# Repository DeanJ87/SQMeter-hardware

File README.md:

# SQMeter Hardware

Hardware source files for the [SQMeter](https://github.com/DeanJ87/SQMeter) open-source sky quality meter.

The main firmware, web UI, and documentation live in the **[SQMeter repo](https://github.com/DeanJ87/SQMeter)**. This repo is the canonical source of truth for the electronics design and manufacturing files.

---

## What's here

| Path | Contents |
|------|----------|
| `hardware/kicad/` | KiCad schematic and PCB source |
| `hardware/exports/` | Generated schematic SVG/PDF and PCB renders |
| `hardware/manufacturing/` | Gerbers, drill files, pick-and-place |
| `hardware/bom/` | Bill of materials (CSV and human-readable) |
| `hardware/ibom/` | InteractiveHtmlBom for assembly |
| `hardware/images/` | Board renders and preview images |
| `scripts/` | Export, BOM, iBOM, and release packaging scripts |

---

## Quick links

| | |
|--|--|
| Main docs site | <https://sqmeter.dev/> |
| Main repo | <https://github.com/DeanJ87/SQMeter> |
| Hardware releases | [Releases](../../releases) |
| Schematic PDF | TODO: link once first release is published |
| Schematic SVG | TODO: link once first release is published |
| BOM CSV | TODO: link once first release is published |
| InteractiveHtmlBom | TODO: link once first release is published |
| Gerbers ZIP | TODO: link once first release is published |

---

## Versioning

Hardware versions follow `vMAJOR.MINOR.PATCH` tied to physical board revisions.

- `v0.x.x` — prototype / bring-up
- `v1.0.0` — first stable public release

Hardware versions are independent of firmware versions. A firmware update does not require a new board revision.

---

## Generating exports locally

Requires KiCad 8 with `kicad-cli` on your PATH.

```bash
./scripts/export-kicad.sh      # schematic SVG/PDF + PCB renders + gerbers
./scripts/generate-bom.sh      # hardware/bom/bom.csv
./scripts/generate-ibom.sh     # hardware/ibom/ibom.html
./scripts/package-release.sh   # dist/SQMeter-Hardware-release.zip
```

---

## 3D printed enclosure

Enclosure files are hosted on Printables (TODO: add link when available). This repo focuses on PCB electronics and manufacturing assets. Mounting dimensions and interface notes may be added under `docs/assembly.md`.

---

## License

[MIT](LICENSE)

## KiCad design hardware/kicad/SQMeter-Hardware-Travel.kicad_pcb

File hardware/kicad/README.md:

# KiCad Project

KiCad 10 projects for the SQMeter boards. All are hardware revision A (`HW_REV` in
`../generator/design.py`), versioned separately from any firmware.

| Project | ESP32 | Power in | For |
|---------|-------|----------|-----|
| `SQMeter-Hardware-ETH.kicad_pro` | Waveshare ESP32-S3-ETH (+ PoE Module B) on 2x20 sockets | PoE or 12 V | Permanent home installs: wired Ethernet, one cable |
| `SQMeter-Hardware-Zero.kicad_pro` | Waveshare ESP32-S3-Zero-M on 2x9 sockets | 12 V | Cheap WiFi home board |
| `SQMeter-Hardware-DevKit.kicad_pro` | ESP32-S3-DevKitC-1-N16R8 on 2x22 sockets | 12 V | WiFi home board, 16 MB flash (always-on red LED) |
| `SQMeter-Hardware.kicad_pro` | ESP32-S3-WROOM-1-N16R8 soldered (JLC) | 12 V or USB-C | Fully assembled WiFi home board |
| `SQMeter-Hardware-Travel.kicad_pro` | Waveshare ESP32-S3-Zero-M on 2x9 sockets | USB-C + 1S Li-ion | Portable unit, 85 x 66 mm, no field wiring |

### GPIO maps

Module, DevKit, Zero and Travel share one map (limited by the Zero, whose 2.54 mm headers carry only
GPIO1-13). The ETH board's W5500 owns GPIO9-14, so it has its own:

| Function | Module / DevKit / Zero | Travel | ETH |
|---|---|---|---|
| RG-15 TX / RX (ESP side) | 1 / 2 | - | 15 / 16 |
| Wind vane (ADC1) / anemometer | 4 / 5 | - | 1 / 2 |
| I2C SDA / SCL (TSL2591 #1, MLX90614, BME280, spare/OLED) | 8 / 9 | 8 / 9 | 17 / 18 |
| I2C-2 SDA / SCL (TSL2591 #2) | 10 / 11 | 10 / 11 | 41 / 42 |
| GPS TX / RX (ESP side) | 12 / 13 | 12 / 13 | 47 / 48 |
| AUX | 6, 7 | 6, 7 | 39, 40 |
| Fuel gauge alert (MAX17048 ALRT, active low) | - | 1 | - |
| Charger STAT1 / STAT2 / PG (open drain, active low) | - | 2 / 4 / 5 | - |
| Status LED | 47 (module only) | Zero RGB 21 | ETH RGB 21 |

### Power

- **12 V boards:** P-FET reverse protection, polyfuse, TVS, AP6320x buck. Plug-in boards are fed 5 V
  through a Schottky and give 3V3 back for the sensors.
- **ETH:** PoE (or the ETH board's USB-C) gives 5 V on its VBUS pin; we feed its VSYS pin (after its own
  diode) from the 12 V buck, so the two never fight. On PoE the RG-15 gets 12.6 V from an MT3608 boost.
- **Travel:** sized for a 1S2P 18650 pack (~7 Ah). USB-C into an MCP73871 power-path charger in adapter
  mode (1.65 A input, backs off if the source sags below 4.55 V): runs the system while charging, 833 mA
  charge (~9 h from empty), safety timer off (it would expire before a 7 Ah pack is full), charges only
  between about 3 and 44 C (NTC on the board). DW01A + two AO3400A protect bare cells (over-charge,
  over-discharge, short). A MAX17048 fuel gauge on the main I2C bus (0x36) reports state of charge %, cell
  voltage and charge/discharge rate; the charger's STAT1/STAT2/PG pins give USB present / charging /
  charged / fault. The power switch cuts the system but not charging. The Zero's own USB-C stays inside for
  recovery flashing. Cells in parallel must be matched (same voltage) before connecting.

All five I2C ports share one JST-XH pinout: **1 GND, 2 3V3, 3 SDA, 4 SCL**. The TSL2591's address is fixed (0x29), so a second
one (SQM + SQM-L) goes on its own bus: the I2C-2 port.

## Files

Generated by `../generator/build.sh <module|devkit|zero>` (see its README); hand-tune in KiCad afterwards.
JLCPCB files (gerber zip, BOM, CPL) come from `../generator/export_jlc.sh <module|devkit|zero>` and land in
`../manufacturing/<project>-rev<X>/`.

Open the `.kicad_pro`, not the `.kicad_sch`/`.kicad_pcb` directly, so library associations resolve.

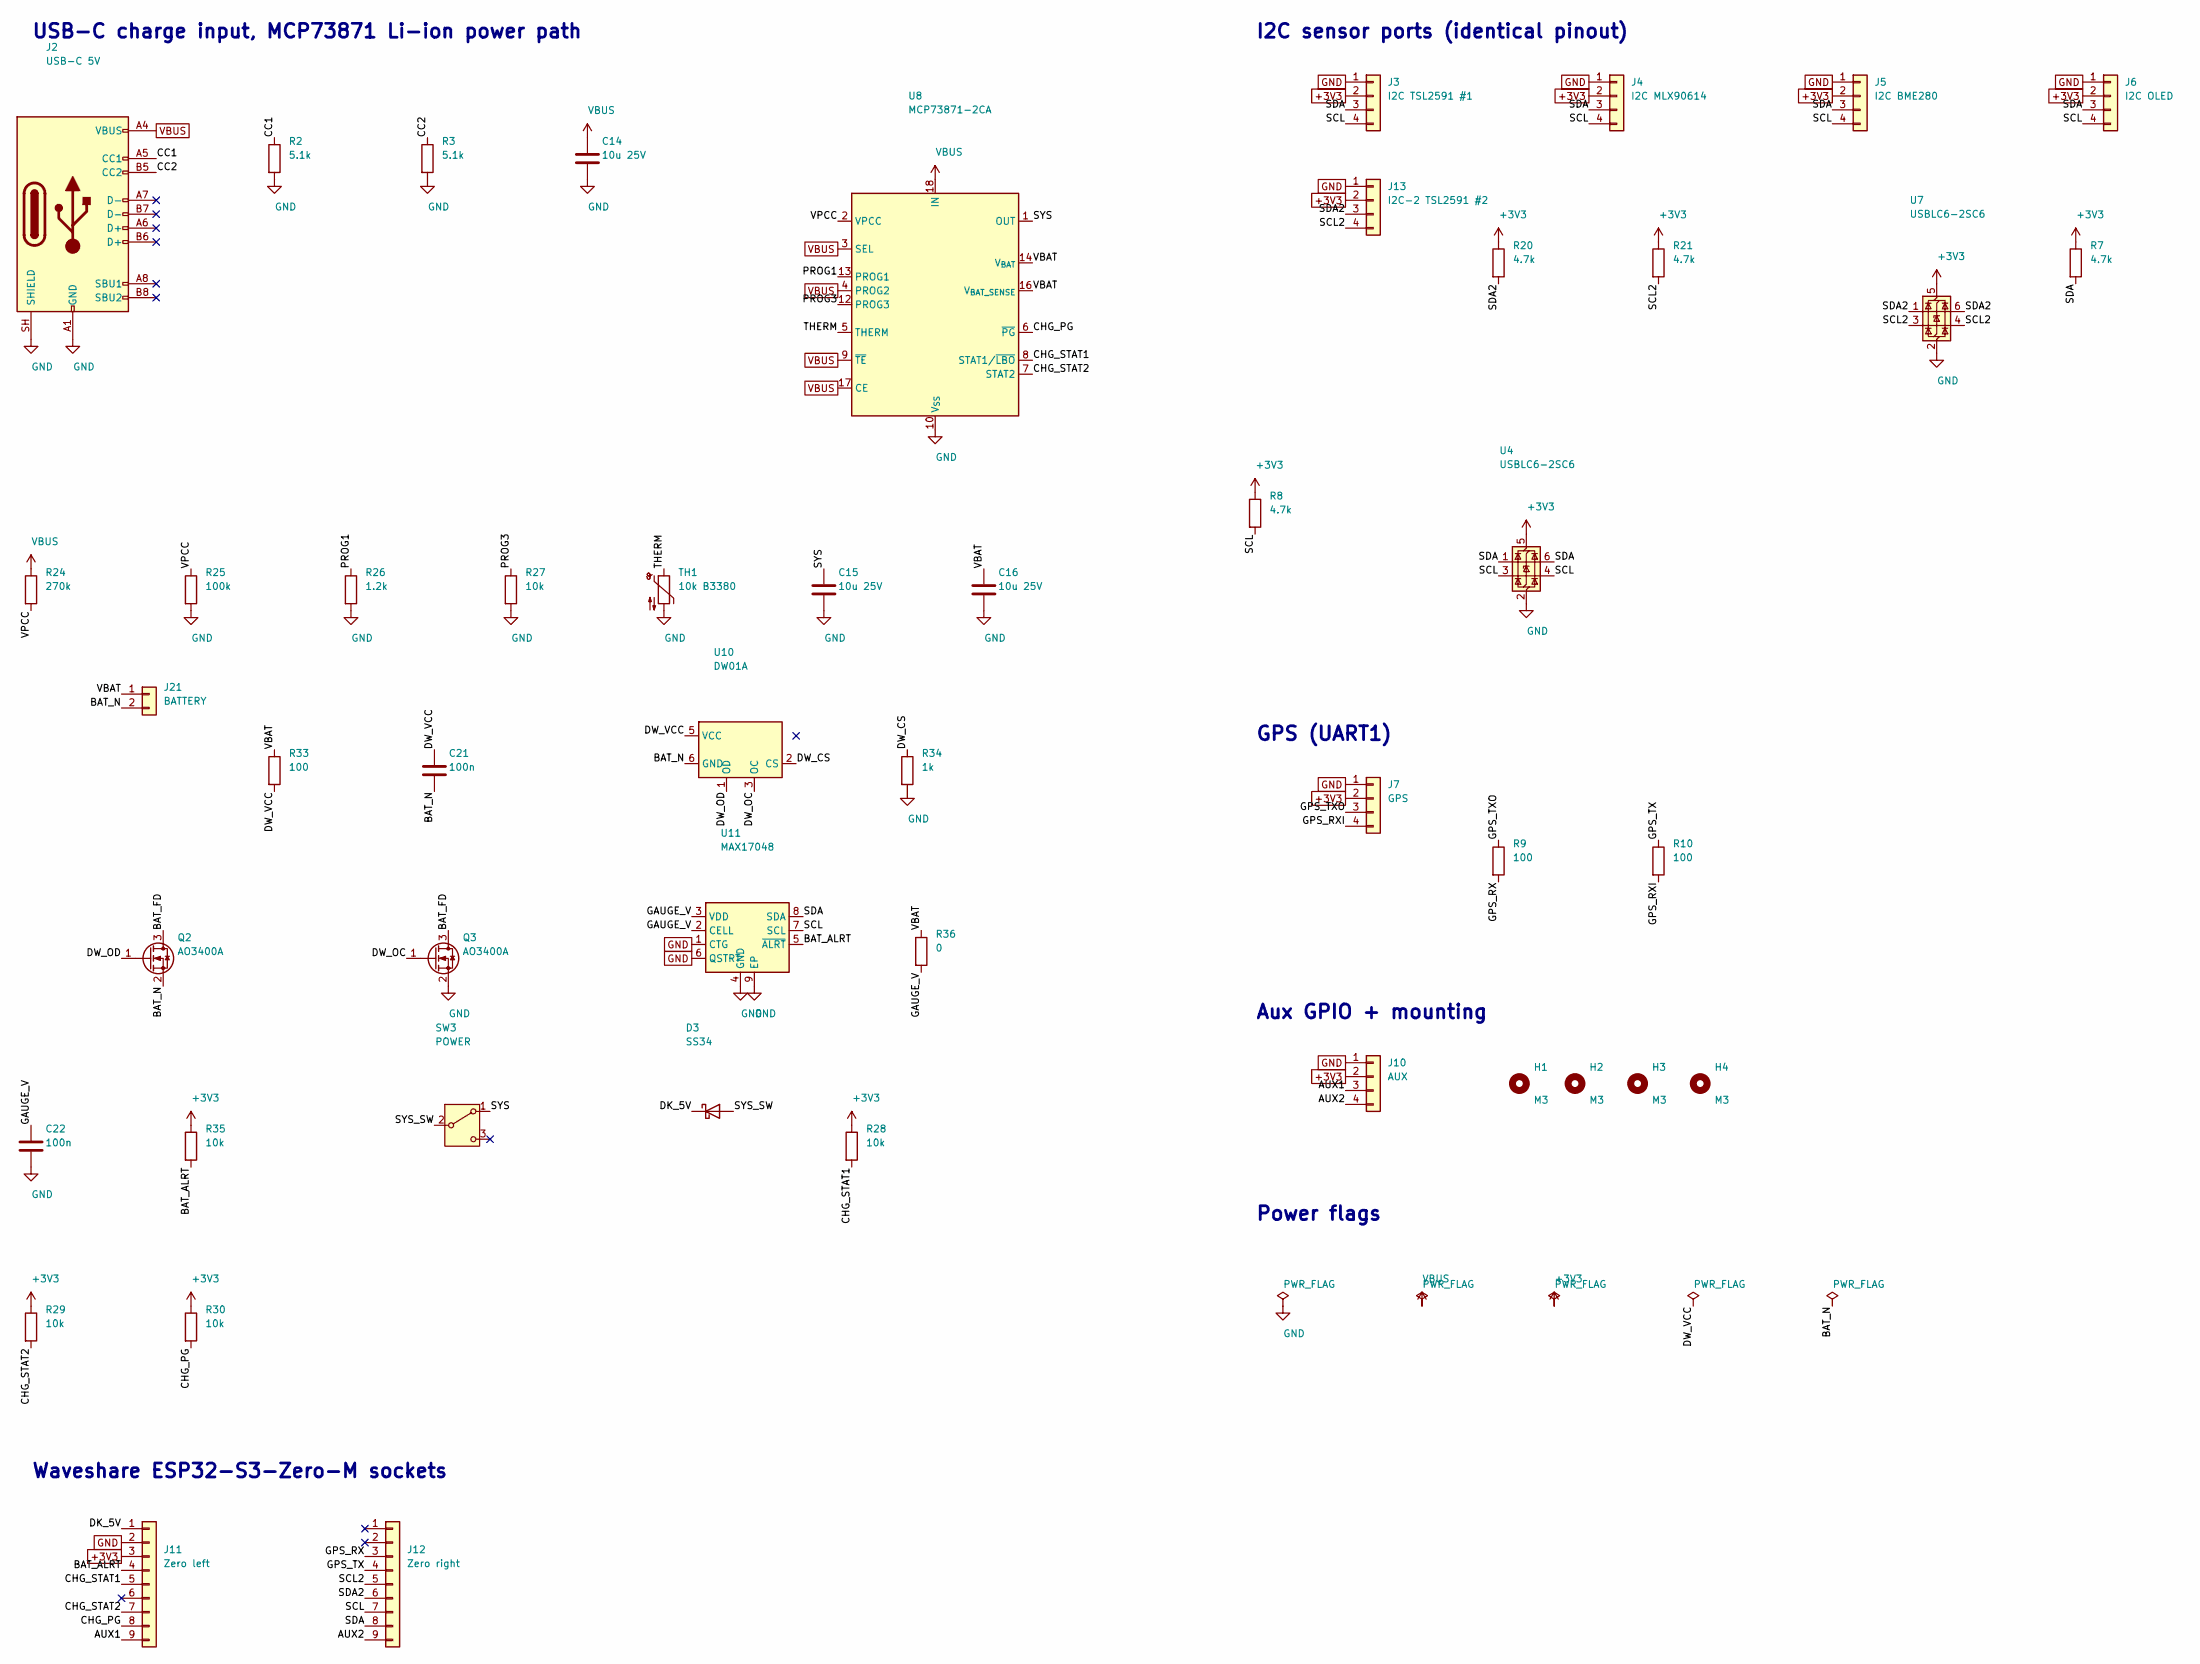
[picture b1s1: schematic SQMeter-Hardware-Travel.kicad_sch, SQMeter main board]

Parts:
C14, C15, C16: 10u 25V; C_0805_2012Metric; LCSC C15850
C21, C22: 100n; C_0603_1608Metric; LCSC C14663
D3: SS34; D_SMA; LCSC C8678
H1, H2, H3, H4: M3; MountingHole_3.2mm_M3
J2: USB-C 5V; USB_C_Receptacle_HRO_TYPE-C-31-M-12; LCSC C165948
J3: I2C TSL2591 #1; JST_XH_B4B-XH-A_1x04_P2.50mm_Vertical; LCSC C144395
J4: I2C MLX90614; JST_XH_B4B-XH-A_1x04_P2.50mm_Vertical; LCSC C144395
J5: I2C BME280; JST_XH_B4B-XH-A_1x04_P2.50mm_Vertical; LCSC C144395
J6: I2C OLED; JST_XH_B4B-XH-A_1x04_P2.50mm_Vertical; LCSC C144395
J7: GPS; JST_XH_B4B-XH-A_1x04_P2.50mm_Vertical; LCSC C144395
J10: AUX; JST_XH_B4B-XH-A_1x04_P2.50mm_Vertical; LCSC C144395
J11: Zero left; PinSocket_1x09_P2.54mm_Vertical; LCSC C22438159
J12: Zero right; PinSocket_1x09_P2.54mm_Vertical; LCSC C22438159
J13: I2C-2 TSL2591 #2; JST_XH_B4B-XH-A_1x04_P2.50mm_Vertical; LCSC C144395
J21: BATTERY; JST_PH_B2B-PH-K_1x02_P2.00mm_Vertical; LCSC C131337
Q2, Q3: AO3400A; SOT-23; LCSC C20917
R2, R3: 5.1k; R_0603_1608Metric; LCSC C23186
R7, R8, R20, R21: 4.7k; R_0603_1608Metric; LCSC C23162
R9, R10, R33: 100; R_0603_1608Metric; LCSC C22775
R24: 270k; R_0603_1608Metric; LCSC C22965
R25: 100k; R_0603_1608Metric; LCSC C25803
R26: 1.2k; R_0603_1608Metric; LCSC C22765
R27, R28, R29, R30, R35: 10k; R_0603_1608Metric; LCSC C25804
R34: 1k; R_0603_1608Metric; LCSC C21190
R36: 0; R_0603_1608Metric; LCSC C21189
SW3: POWER; SW_SPDT_Shouhan_MSK12C02; LCSC C431540
TH1: 10k B3380; R_0603_1608Metric; LCSC C13564
U4, U7: USBLC6-2SC6; SOT-23-6; LCSC C7519
U8: MCP73871-2CA; QFN-20-1EP_4x4mm_P0.5mm_EP2.5x2.5mm_ThermalVias; LCSC C185603
U10: DW01A; SOT-23-6; LCSC C351410
U11: MAX17048; TDFN-8-1EP_2x2mm_P0.5mm_EP0.8x1.2mm; LCSC C2682616

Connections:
+3V3: J3.2, J4.2, J5.2, J6.2, J7.2, J10.2, J11.3, J13.2, R7.1, R8.1, R20.1, R21.1, R28.1, R29.1, R30.1, R35.1, U4.5 (VBUS), U7.5 (VBUS)
/AUX1: J10.3, J11.9
/AUX2: J10.4, J12.9
/BAT_ALRT: J11.4, R35.2, U11.5 (~ALRT)
/BAT_FD: Q2.3 (D), Q3.3 (D)
/BAT_N: C21.2, J21.2, Q2.2 (S), U10.6 (GND)
/CC1: J2.A5 (CC1), R2.1
/CC2: J2.B5 (CC2), R3.1
/CHG_PG: J11.8, R30.2, U8.6 (~PG)
/CHG_STAT1: J11.5, R28.2, U8.8 (STAT1/~LBO)
/CHG_STAT2: J11.7, R29.2, U8.7 (STAT2)
/DK_5V: D3.1 (K), J11.1
/DW_CS: R34.1, U10.2 (CS)
/DW_OC: Q3.1 (G), U10.3 (OC)
/DW_OD: Q2.1 (G), U10.1 (OD)
/DW_VCC: C21.1, R33.2, U10.5 (VCC)
/GAUGE_V: C22.1, R36.2, U11.2 (CELL), U11.3 (VDD)
/GPS_RX: J12.3, R9.2
/GPS_RXI: J7.4, R10.2
/GPS_TX: J12.4, R10.1
/GPS_TXO: J7.3, R9.1
/PROG1: R26.1, U8.13 (PROG1)
/PROG3: R27.1, U8.12 (PROG3)
/SCL: J3.4, J4.4, J5.4, J6.4, J12.7, R8.2, U4.3 (I/O2), U4.4 (I/O2), U11.7 (SCL)
/SCL2: J12.5, J13.4, R21.2, U7.3 (I/O2), U7.4 (I/O2)
/SDA: J3.3, J4.3, J5.3, J6.3, J12.8, R7.2, U4.1 (I/O1), U4.6 (I/O1), U11.8 (SDA)
/SDA2: J12.6, J13.3, R20.2, U7.1 (I/O1), U7.6 (I/O1)
/SYS: C15.1, SW3.1 (A), U8.1 (OUT), U8.20 (OUT)
/SYS_SW: D3.2 (A), SW3.2 (B)
/THERM: TH1.1, U8.5 (THERM)
/VBAT: C16.1, J21.1, R33.1, R36.1, U8.14 (V_{BAT}), U8.15 (V_{BAT}), U8.16 (V_{BAT_SENSE})
/VPCC: R24.2, R25.1, U8.2 (VPCC)
GND: C14.2, C15.2, C16.2, C22.2, J2.A1 (GND), J2.A12 (GND), J2.B1 (GND), J2.B12 (GND), J2.SH (SHIELD), J3.1, J4.1, J5.1, J6.1, J7.1, J10.1, J11.2, J13.1, Q3.2 (S), R2.2, R3.2, R25.2, R26.2, R27.2, R34.2, TH1.2, U4.2 (GND), U7.2 (GND), U8.10 (V_{SS}), U8.11 (V_{SS}), U8.21 (V_{SS}), U11.1 (CTG), U11.4 (GND), U11.6 (QSTRT), U11.9 (EP)
VBUS: C14.1, J2.A4 (VBUS), J2.A9 (VBUS), J2.B4 (VBUS), J2.B9 (VBUS), R24.1, U8.3 (SEL), U8.4 (PROG2), U8.9 (~TE), U8.17 (CE), U8.18 (IN), U8.19 (IN)

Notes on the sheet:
USB-C charge input, MCP73871 Li-ion power path
Waveshare ESP32-S3-Zero-M sockets
I2C sensor ports (identical pinout)
GPS (UART1)
Aux GPIO + mounting
Power flags

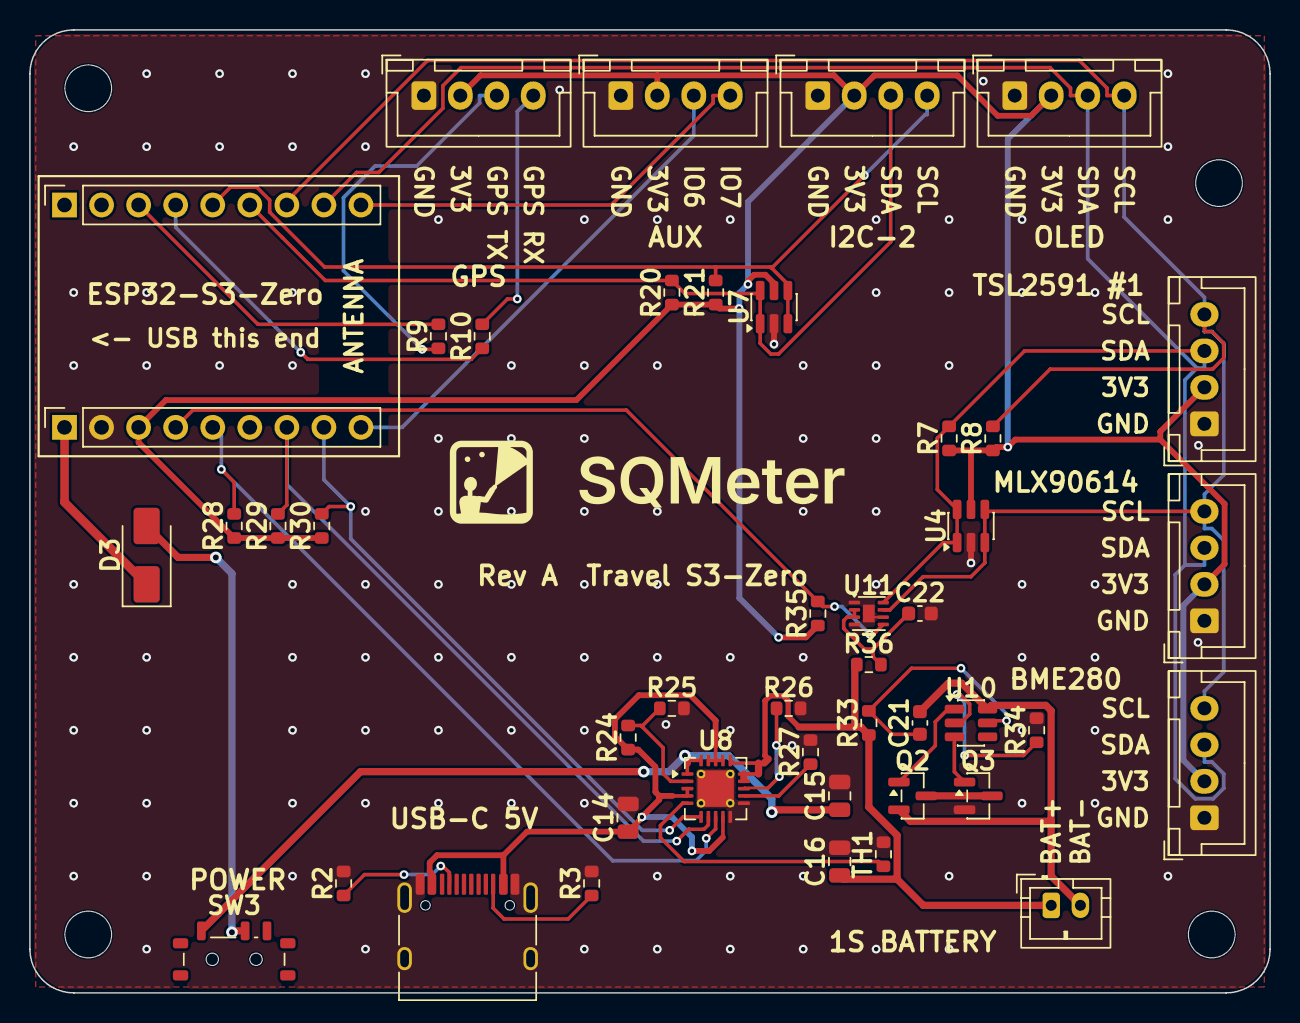
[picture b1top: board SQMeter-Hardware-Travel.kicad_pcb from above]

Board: 2 copper layers, 85.0 x 66.0 mm, 49 parts (0 on the bottom side), 34 nets.

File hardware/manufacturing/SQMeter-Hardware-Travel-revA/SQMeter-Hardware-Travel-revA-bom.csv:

Comment,Designator,Footprint,LCSC Part #
10u 25V,"C14,C15,C16",C_0805_2012Metric,C15850
100n,"C21,C22",C_0603_1608Metric,C14663
SS34,D3,D_SMA,C8678
USB-C 5V,J2,USB_C_Receptacle_HRO_TYPE-C-31-M-12,C165948
I2C TSL2591 #1,J3,JST_XH_B4B-XH-A_1x04_P2.50mm_Vertical,C144395
I2C MLX90614,J4,JST_XH_B4B-XH-A_1x04_P2.50mm_Vertical,C144395
I2C BME280,J5,JST_XH_B4B-XH-A_1x04_P2.50mm_Vertical,C144395
I2C OLED,J6,JST_XH_B4B-XH-A_1x04_P2.50mm_Vertical,C144395
GPS,J7,JST_XH_B4B-XH-A_1x04_P2.50mm_Vertical,C144395
AUX,J10,JST_XH_B4B-XH-A_1x04_P2.50mm_Vertical,C144395
Zero left,J11,PinSocket_1x09_P2.54mm_Vertical,C22438159
Zero right,J12,PinSocket_1x09_P2.54mm_Vertical,C22438159
I2C-2 TSL2591 #2,J13,JST_XH_B4B-XH-A_1x04_P2.50mm_Vertical,C144395
BATTERY,J21,JST_PH_B2B-PH-K_1x02_P2.00mm_Vertical,C131337
AO3400A,"Q2,Q3",SOT-23,C20917
5.1k,"R2,R3",R_0603_1608Metric,C23186
4.7k,"R7,R8,R20,R21",R_0603_1608Metric,C23162
100,"R9,R10,R33",R_0603_1608Metric,C22775
270k,R24,R_0603_1608Metric,C22965
100k,R25,R_0603_1608Metric,C25803
1.2k,R26,R_0603_1608Metric,C22765
10k,"R27,R28,R29,R30,R35",R_0603_1608Metric,C25804
1k,R34,R_0603_1608Metric,C21190
0,R36,R_0603_1608Metric,C21189
POWER,SW3,SW_SPDT_Shouhan_MSK12C02,C431540
10k B3380,TH1,R_0603_1608Metric,C13564
USBLC6-2SC6,"U4,U7",SOT-23-6,C7519
MCP73871-2CA,U8,QFN-20-1EP_4x4mm_P0.5mm_EP2.5x2.5mm_ThermalVias,C185603
DW01A,U10,SOT-23-6,C351410
MAX17048,U11,TDFN-8-1EP_2x2mm_P0.5mm_EP0.8x1.2mm,C2682616

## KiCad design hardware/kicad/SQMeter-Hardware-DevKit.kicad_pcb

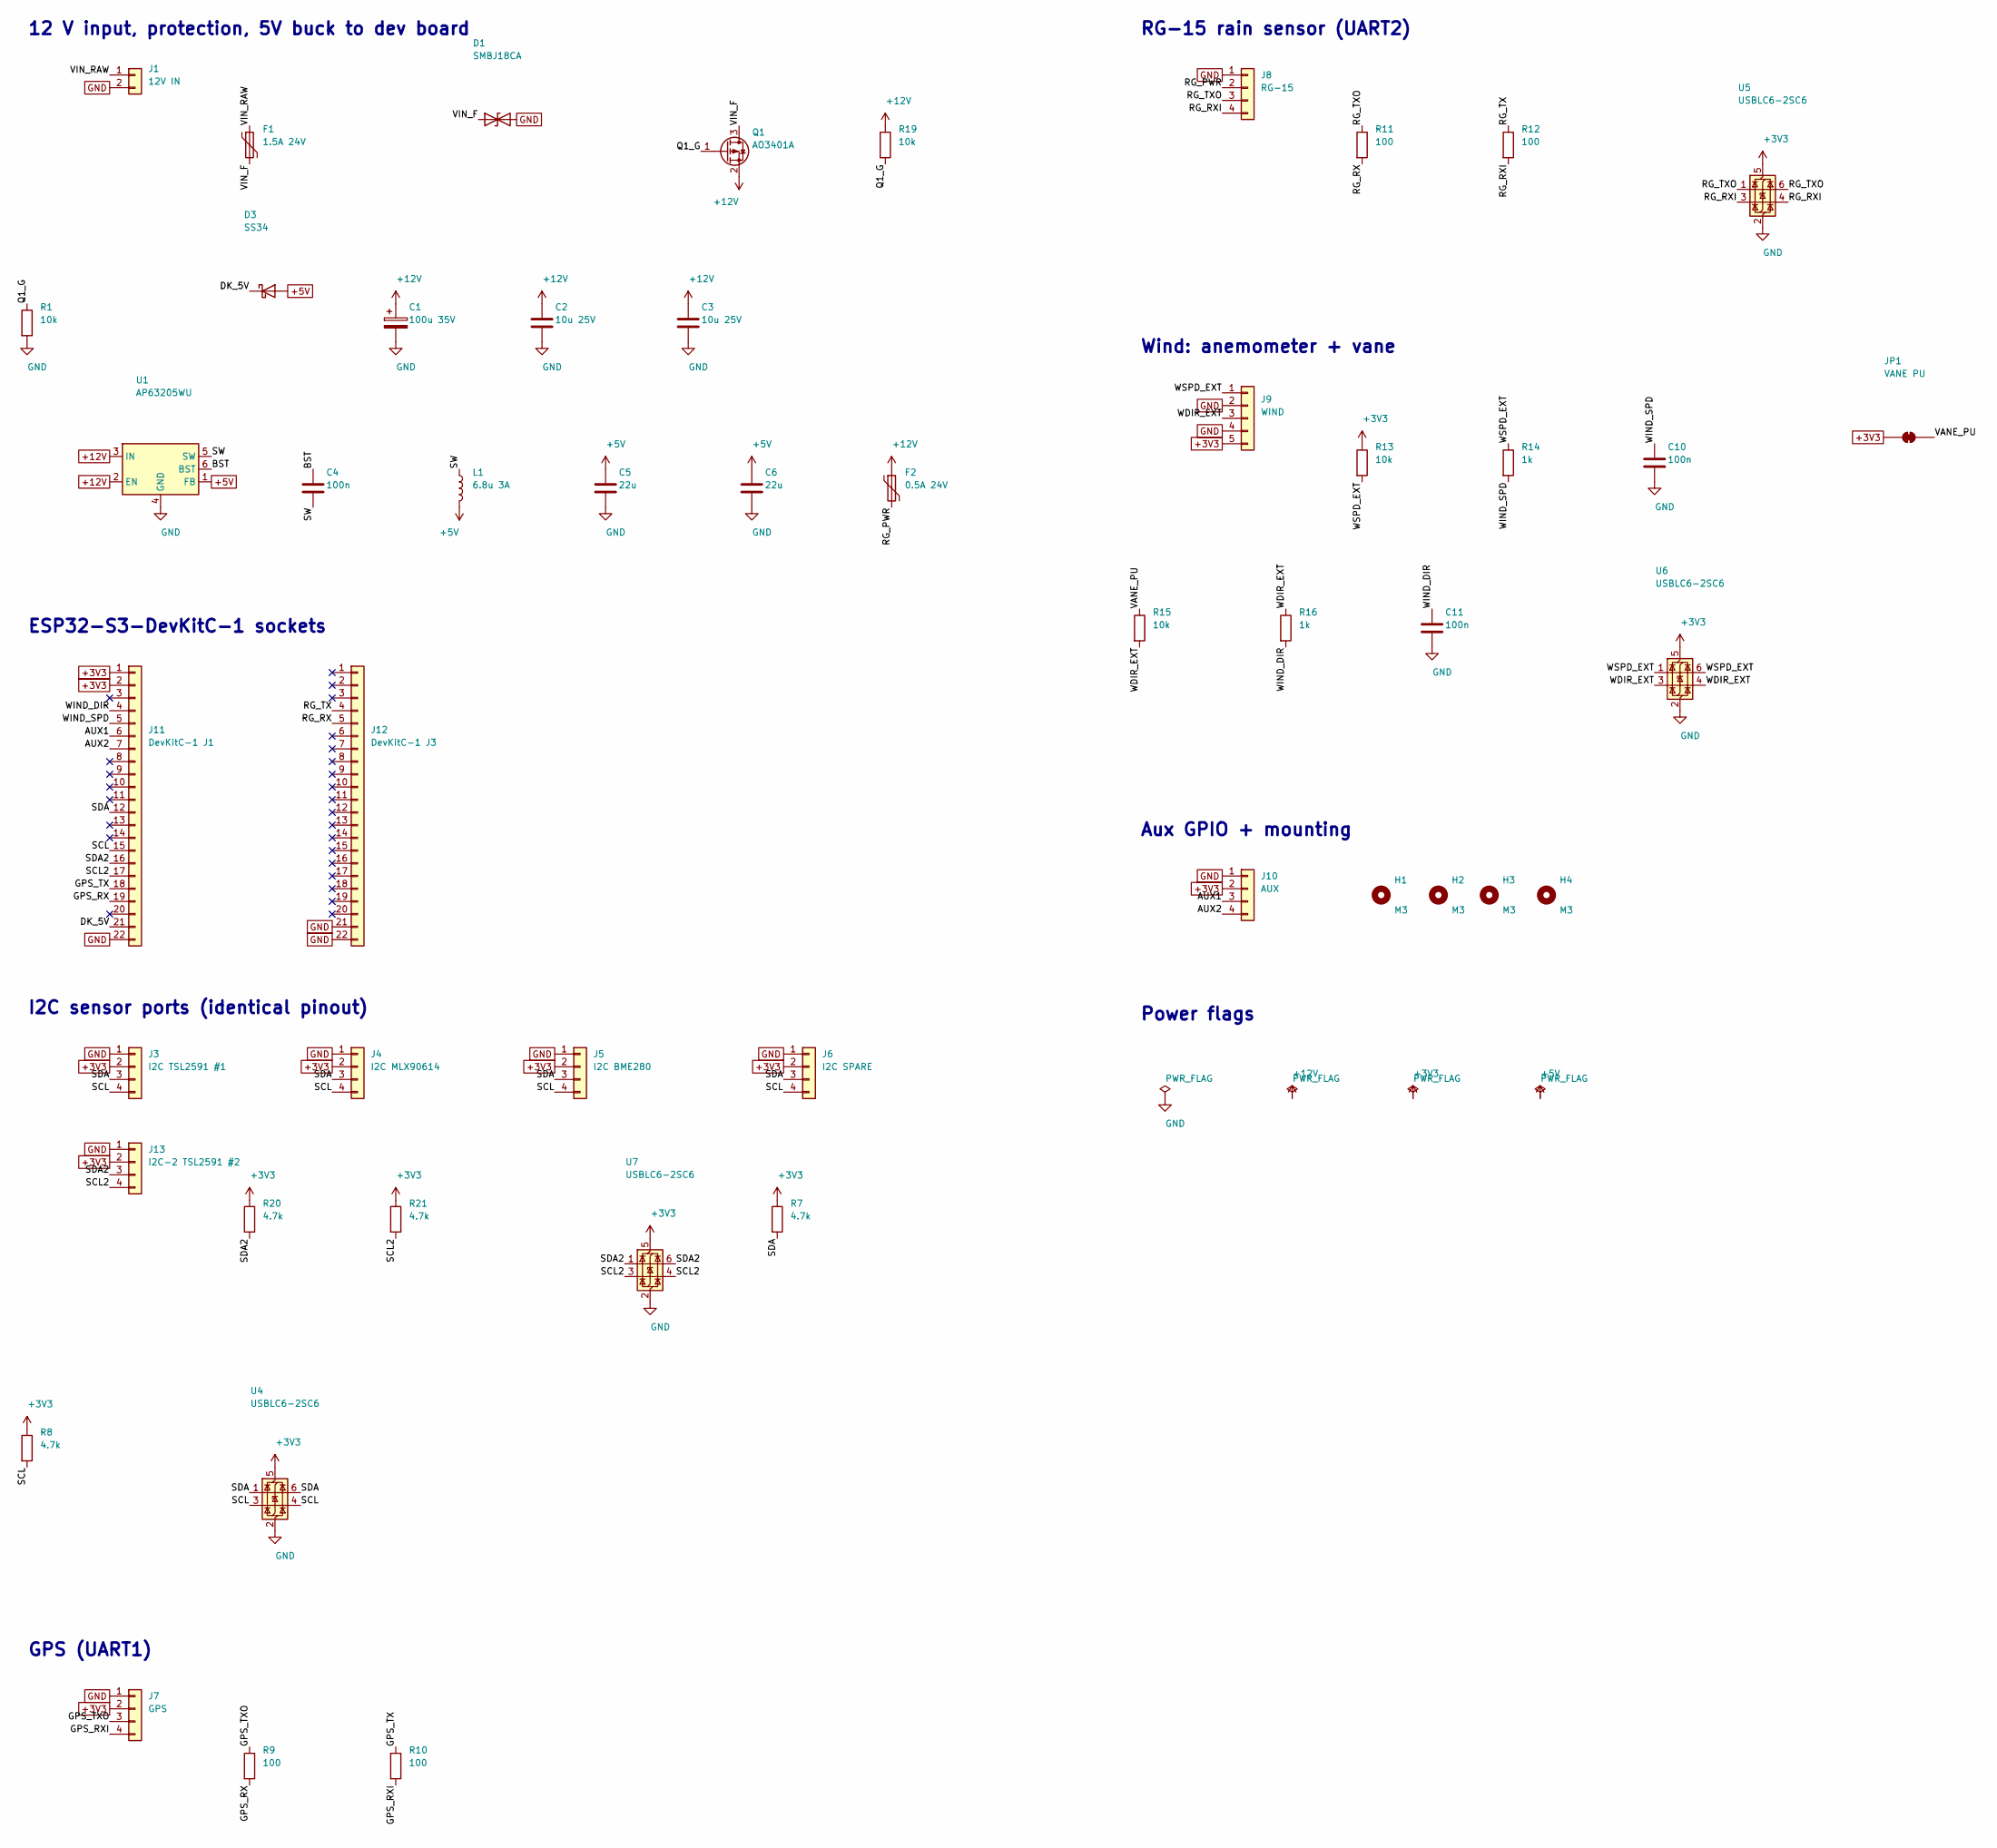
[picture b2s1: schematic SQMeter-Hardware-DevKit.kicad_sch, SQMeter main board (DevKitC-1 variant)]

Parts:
C1: 100u 35V; CP_Elec_8x10; LCSC C165636
C2, C3: 10u 25V; C_0805_2012Metric; LCSC C15850
C4, C10, C11: 100n; C_0603_1608Metric; LCSC C14663
C5, C6: 22u; C_0805_2012Metric; LCSC C45783
D1: SMBJ18CA; D_SMB; LCSC C78413
D3: SS34; D_SMA; LCSC C8678
F1: 1.5A 24V; Fuse_1812_4532Metric; LCSC C32404
F2: 0.5A 24V; Fuse_1206_3216Metric; LCSC C492011
H1, H2, H3, H4: M3; MountingHole_3.2mm_M3
J1: 12V IN; PhoenixContact_MSTBA_2,5_2-G-5,08_1x02_P5.08mm_Horizontal; LCSC C3697
J3: I2C TSL2591 #1; JST_XH_B4B-XH-A_1x04_P2.50mm_Vertical; LCSC C144395
J4: I2C MLX90614; JST_XH_B4B-XH-A_1x04_P2.50mm_Vertical; LCSC C144395
J5: I2C BME280; JST_XH_B4B-XH-A_1x04_P2.50mm_Vertical; LCSC C144395
J6: I2C SPARE; JST_XH_B4B-XH-A_1x04_P2.50mm_Vertical; LCSC C144395
J7: GPS; JST_XH_B4B-XH-A_1x04_P2.50mm_Vertical; LCSC C144395
J8: RG-15; PhoenixContact_MC_1,5_4-G-3.5_1x04_P3.50mm_Horizontal; LCSC C5188297
J9: WIND; PhoenixContact_MC_1,5_5-G-3.5_1x05_P3.50mm_Horizontal; LCSC C5188298
J10: AUX; JST_XH_B4B-XH-A_1x04_P2.50mm_Vertical; LCSC C144395
J11: DevKitC-1 J1; PinSocket_1x22_P2.54mm_Vertical; LCSC C41376161
J12: DevKitC-1 J3; PinSocket_1x22_P2.54mm_Vertical; LCSC C41376161
J13: I2C-2 TSL2591 #2; JST_XH_B4B-XH-A_1x04_P2.50mm_Vertical; LCSC C144395
JP1: VANE PU; SolderJumper-2_P1.3mm_Bridged_RoundedPad1.0x1.5mm
L1: 6.8u 3A; L_Sunlord_SWPA6045S; LCSC C57254
Q1: AO3401A; SOT-23; LCSC C15127
R1, R13, R15, R19: 10k; R_0603_1608Metric; LCSC C25804
R7, R8, R20, R21: 4.7k; R_0603_1608Metric; LCSC C23162
R9, R10, R11, R12: 100; R_0603_1608Metric; LCSC C22775
R14, R16: 1k; R_0603_1608Metric; LCSC C21190
U1: AP63205WU; TSOT-23-6; LCSC C2071056
U4, U5, U6, U7: USBLC6-2SC6; SOT-23-6; LCSC C7519

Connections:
+3V3: J3.2, J4.2, J5.2, J6.2, J7.2, J9.5, J10.2, J11.1, J11.2, J13.2, JP1.1 (A), R7.1, R8.1, R13.1, R20.1, R21.1, U4.5 (VBUS), U5.5 (VBUS), U6.5 (VBUS), U7.5 (VBUS)
+5V: C5.1, C6.1, D3.2 (A), L1.2, U1.1 (FB)
+12V: C1.1, C2.1, C3.1, F2.1, Q1.2 (S), R19.1, U1.2 (EN), U1.3 (IN)
/AUX1: J10.3, J11.6
/AUX2: J10.4, J11.7
/BST: C4.1, U1.6 (BST)
/DK_5V: D3.1 (K), J11.21
/GPS_RX: J11.19, R9.2
/GPS_RXI: J7.4, R10.2
/GPS_TX: J11.18, R10.1
/GPS_TXO: J7.3, R9.1
/Q1_G: Q1.1 (G), R1.1, R19.2
/RG_PWR: F2.2, J8.2
/RG_RX: J12.5, R11.2
/RG_RXI: J8.4, R12.2, U5.3 (I/O2), U5.4 (I/O2)
/RG_TX: J12.4, R12.1
/RG_TXO: J8.3, R11.1, U5.1 (I/O1), U5.6 (I/O1)
/SCL: J3.4, J4.4, J5.4, J6.4, J11.15, R8.2, U4.3 (I/O2), U4.4 (I/O2)
/SCL2: J11.17, J13.4, R21.2, U7.3 (I/O2), U7.4 (I/O2)
/SDA: J3.3, J4.3, J5.3, J6.3, J11.12, R7.2, U4.1 (I/O1), U4.6 (I/O1)
/SDA2: J11.16, J13.3, R20.2, U7.1 (I/O1), U7.6 (I/O1)
/SW: C4.2, L1.1, U1.5 (SW)
/VANE_PU: JP1.2 (B), R15.1
/VIN_F: D1.1 (A1), F1.2, Q1.3 (D)
/VIN_RAW: F1.1, J1.1
/WDIR_EXT: J9.3, R15.2, R16.1, U6.3 (I/O2), U6.4 (I/O2)
/WIND_DIR: C11.1, J11.4, R16.2
/WIND_SPD: C10.1, J11.5, R14.2
/WSPD_EXT: J9.1, R13.2, R14.1, U6.1 (I/O1), U6.6 (I/O1)
GND: C1.2, C2.2, C3.2, C5.2, C6.2, C10.2, C11.2, D1.2 (A2), J1.2, J3.1, J4.1, J5.1, J6.1, J7.1, J8.1, J9.2, J9.4, J10.1, J11.22, J12.21, J12.22, J13.1, R1.2, U1.4 (GND), U4.2 (GND), U5.2 (GND), U6.2 (GND), U7.2 (GND)

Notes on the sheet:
12 V input, protection, 5V buck to dev board
ESP32-S3-DevKitC-1 sockets
I2C sensor ports (identical pinout)
GPS (UART1)
RG-15 rain sensor (UART2)
Wind: anemometer + vane
Aux GPIO + mounting
Power flags

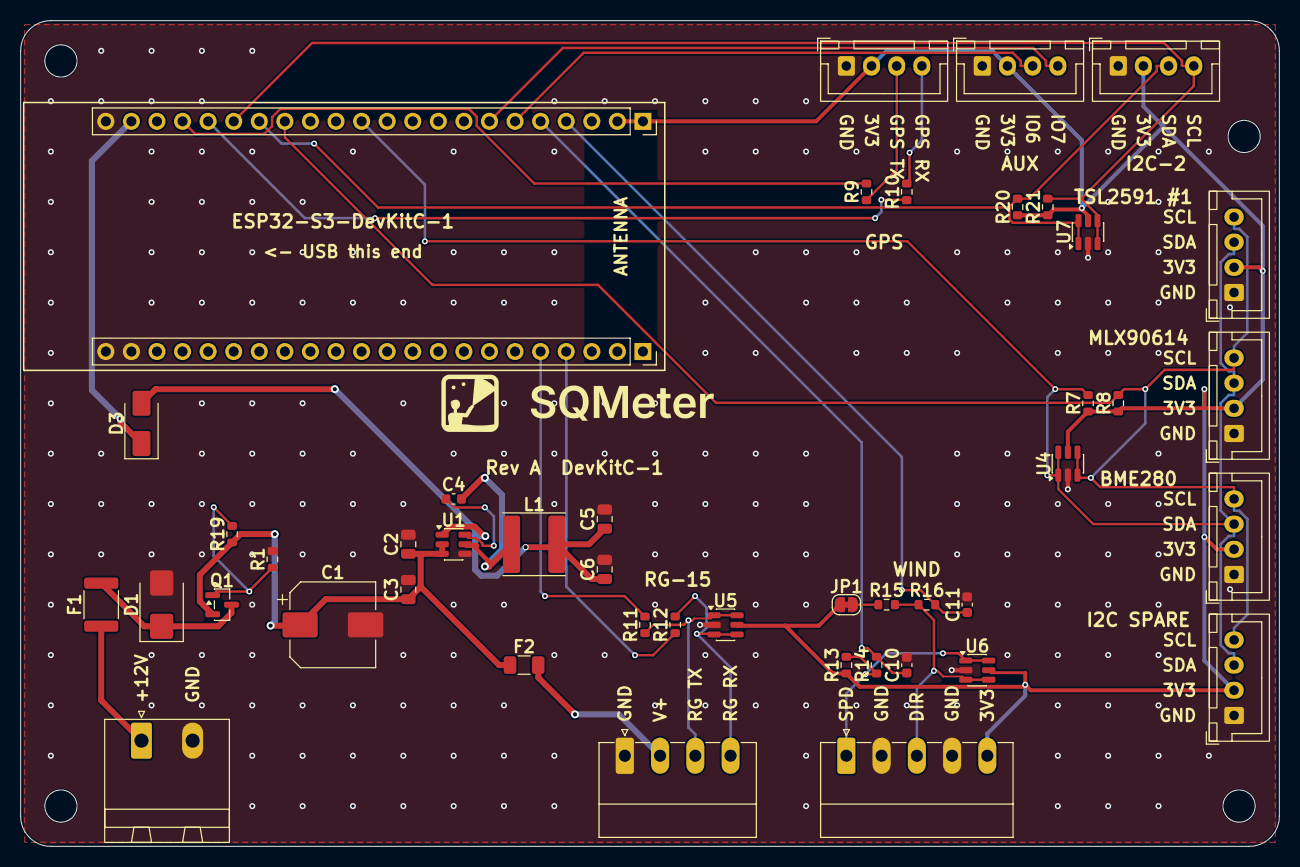
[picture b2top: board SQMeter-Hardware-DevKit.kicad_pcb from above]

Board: 2 copper layers, 125.0 x 82.0 mm, 50 parts (0 on the bottom side), 30 nets.

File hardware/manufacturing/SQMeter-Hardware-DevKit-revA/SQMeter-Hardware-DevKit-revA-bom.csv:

Comment,Designator,Footprint,LCSC Part #
100u 35V,C1,CP_Elec_8x10,C165636
10u 25V,"C2,C3",C_0805_2012Metric,C15850
100n,"C4,C10,C11",C_0603_1608Metric,C14663
22u,"C5,C6",C_0805_2012Metric,C45783
SMBJ18CA,D1,D_SMB,C78413
SS34,D3,D_SMA,C8678
1.5A 24V,F1,Fuse_1812_4532Metric,C32404
0.5A 24V,F2,Fuse_1206_3216Metric,C492011
12V IN,J1,"PhoenixContact_MSTBA_2,5_2-G-5,08_1x02_P5.08mm_Horizontal",C3697
I2C TSL2591 #1,J3,JST_XH_B4B-XH-A_1x04_P2.50mm_Vertical,C144395
I2C MLX90614,J4,JST_XH_B4B-XH-A_1x04_P2.50mm_Vertical,C144395
I2C BME280,J5,JST_XH_B4B-XH-A_1x04_P2.50mm_Vertical,C144395
I2C SPARE,J6,JST_XH_B4B-XH-A_1x04_P2.50mm_Vertical,C144395
GPS,J7,JST_XH_B4B-XH-A_1x04_P2.50mm_Vertical,C144395
RG-15,J8,"PhoenixContact_MC_1,5_4-G-3.5_1x04_P3.50mm_Horizontal",C5188297
WIND,J9,"PhoenixContact_MC_1,5_5-G-3.5_1x05_P3.50mm_Horizontal",C5188298
AUX,J10,JST_XH_B4B-XH-A_1x04_P2.50mm_Vertical,C144395
DevKitC-1 J1,J11,PinSocket_1x22_P2.54mm_Vertical,C41376161
DevKitC-1 J3,J12,PinSocket_1x22_P2.54mm_Vertical,C41376161
I2C-2 TSL2591 #2,J13,JST_XH_B4B-XH-A_1x04_P2.50mm_Vertical,C144395
6.8u 3A,L1,L_Sunlord_SWPA6045S,C57254
AO3401A,Q1,SOT-23,C15127
10k,"R1,R13,R15,R19",R_0603_1608Metric,C25804
4.7k,"R7,R8,R20,R21",R_0603_1608Metric,C23162
100,"R9,R10,R11,R12",R_0603_1608Metric,C22775
1k,"R14,R16",R_0603_1608Metric,C21190
AP63205WU,U1,TSOT-23-6,C2071056
USBLC6-2SC6,"U4,U5,U6,U7",SOT-23-6,C7519

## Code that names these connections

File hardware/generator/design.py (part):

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# GPIO1-13 (+43/44 console); GPIO3 is a strapping pin, so 1,2,4-13 are the twelve usable pins.
GPIO_MAP = {
    1: 'RG_TX', 2: 'RG_RX',          # UART to RG-15
    4: 'WIND_DIR', 5: 'WIND_SPD',    # vane must be ADC1 (GPIO1-10)
    6: 'AUX1', 7: 'AUX2',
    10: 'SDA2', 11: 'SCL2',          # second I2C bus: a second TSL2591 (both are fixed at 0x29)
    8: 'SDA', 9: 'SCL',
    12: 'GPS_TX', 13: 'GPS_RX',      # UART to GPS
}
if TRAVEL:  # no RG-15 or wind: those pins report the battery and charger instead
    GPIO_MAP.update({1: 'BAT_ALRT', 2: 'CHG_STAT1', 4: 'CHG_STAT2', 5: 'CHG_PG'})
if ETH:     # W5500 owns GPIO9-14, SD card 4-7, octal PSRAM 33-37, USB 19/20, RGB LED 21
    GPIO_MAP = {1: 'WIND_DIR', 2: 'WIND_SPD', 15: 'RG_TX', 16: 'RG_RX', 17: 'SDA', 18: 'SCL',
                39: 'AUX1', 40: 'AUX2', 41: 'SDA2', 42: 'SCL2', 47: 'GPS_TX', 48: 'GPS_RX'}
AUX_GPIO = [g for n in ('AUX1', 'AUX2') for g, v in GPIO_MAP.items() if v == n]

POWER_NETS = {'GND': 'power:GND', '+3V3': 'power:+3V3', '+12V': 'power:+12V', 'VBUS': 'power:VBUS', '+5V': 'power:+5V'}

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        P('SW3', 'Switch:SW_SPDT', 'POWER', 'Button_Switch_SMD:SW_SPDT_Shouhan_MSK12C02',
          {'1': 'SYS', '2': 'SYS_SW', '3': None}, 'C431540', 'Power switch; charging still works when off'),
        P('D3', 'Device:D_Schottky', 'SS34', 'Diode_SMD:D_SMA', {'1': 'DK_5V', '2': 'SYS_SW'}, 'C8678',
          'Into the Zero 5V pin; stops a PC on the Zero USB-C pushing into SYS'),
        R('R28', '10k', '+3V3', 'CHG_STAT1', 'C25804'),
        R('R29', '10k', '+3V3', 'CHG_STAT2', 'C25804'),
        R('R30', '10k', '+3V3', 'CHG_PG', 'C25804'),
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
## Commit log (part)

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2026-04-26 chore: initial repository scaffold
    Directory structure, docs, scripts, and CI workflows for the SQMeter
    hardware repo. KiCad project files not yet included — scaffold only.
